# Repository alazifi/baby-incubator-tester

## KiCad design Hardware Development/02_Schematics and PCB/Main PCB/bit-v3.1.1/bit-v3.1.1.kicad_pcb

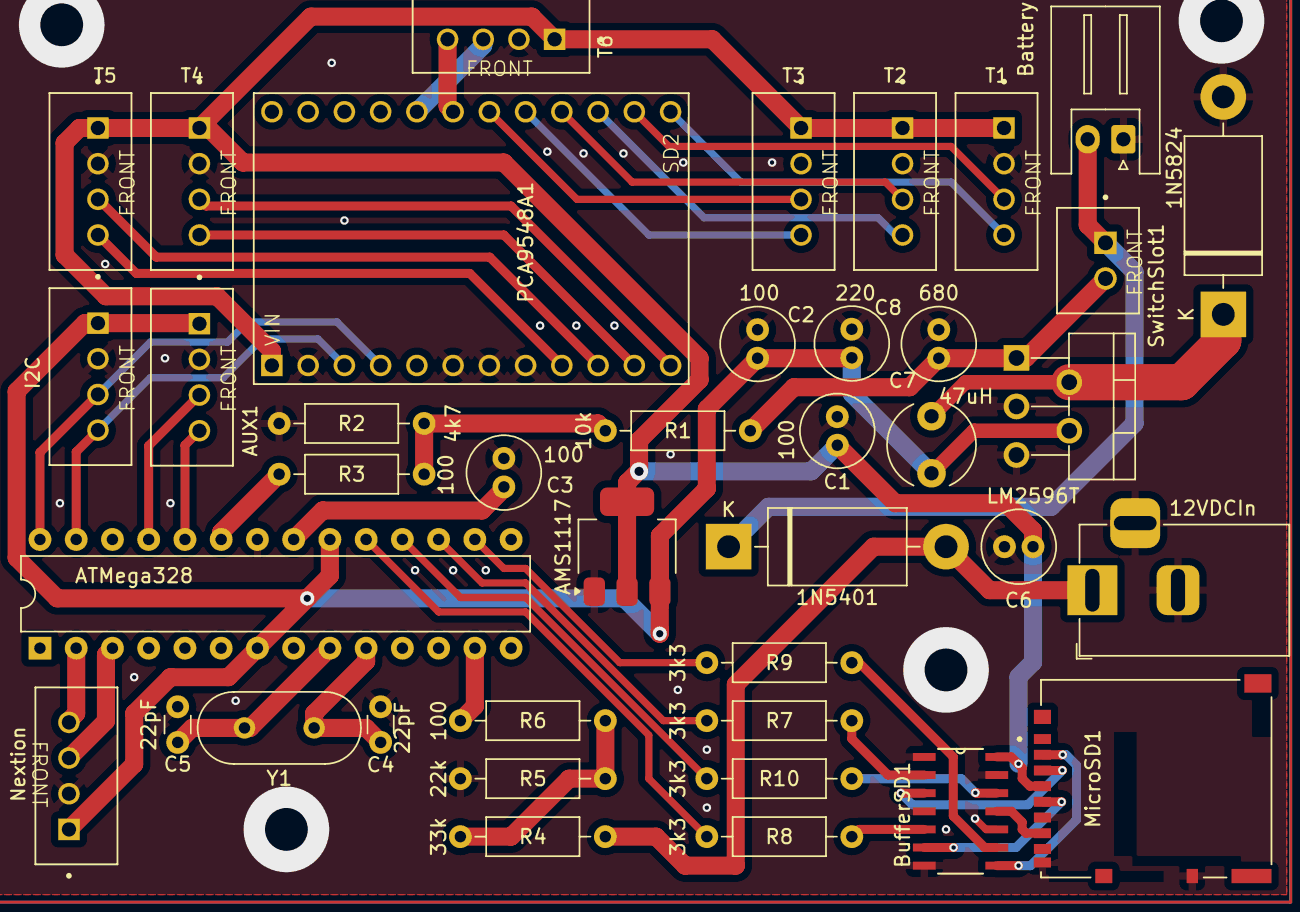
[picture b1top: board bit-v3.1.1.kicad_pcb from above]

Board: 2 copper layers, 40 parts (0 on the bottom side), 44 nets.

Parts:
1N5401: 1N5401; D_DO-201AD_P15.24mm_Horizontal
1N5824: 1N5824; D_DO-201AD_P15.24mm_Horizontal
12VDCIn: 12VDC In; BarrelJack_Horizontal
47uH: 47; L_Radial_D6.0mm_P4.00mm
AMS1117: AMS1117; SOT-223-3_TabPin2
ATMega328: ATmega328P-P; DIP-28_W7.62mm
AUX1: AUX; JST_B4B-XH-A_LF__SN_
Battery: Battery; JST_XH_S2B-XH-A_1x02_P2.50mm_Horizontal
BufferSD1: IC-SD; SOIC127P600X175-14N
C1, C2, C3, C6: 100; C_Radial_D5.0mm_H11.0mm_P2.00mm
C4, C5: 22pF; C_Disc_D3.0mm_W1.6mm_P2.50mm
C7: 680; C_Radial_D5.0mm_H11.0mm_P2.00mm
C8: 220; C_Radial_D5.0mm_H11.0mm_P2.00mm
I2C: I2C; JST_B4B-XH-A_LF__SN_
LM2596T: LM2596T-5; TO-220-5_P3.4x3.7mm_StaggerOdd_Lead3.8mm_Vertical
MicroSD1: MicroSD; HRS_DM3AT-SF-PEJM5
Nextion: Nextion; JST_B4B-XH-A_LF__SN_
PCA9548A1: PCA9548A_Board; PCA9548A
R1: 10k; R_Axial_DIN0207_L6.3mm_D2.5mm_P10.16mm_Horizontal
R2: 4k7; R_Axial_DIN0207_L6.3mm_D2.5mm_P10.16mm_Horizontal
R3, R6: 100; R_Axial_DIN0207_L6.3mm_D2.5mm_P10.16mm_Horizontal
R4: 33k; R_Axial_DIN0207_L6.3mm_D2.5mm_P10.16mm_Horizontal
R5: 22k; R_Axial_DIN0207_L6.3mm_D2.5mm_P10.16mm_Horizontal
R7, R8, R9, R10: 3k3; R_Axial_DIN0207_L6.3mm_D2.5mm_P10.16mm_Horizontal
SwitchSlot1: Switch; JST_B2B-XH-A
T1: T1; JST_B4B-XH-A_LF__SN_
T2: T2; JST_B4B-XH-A_LF__SN_
T3: T3; JST_B4B-XH-A_LF__SN_
T4: T4; JST_B4B-XH-A_LF__SN_
T5: T5; JST_B4B-XH-A_LF__SN_
T6: T6; JST_B4B-XH-A_LF__SN_
Y1: Crystal; Crystal_HC49-4H_Vertical

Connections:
3V3DC: AMS1117.2 (VO), BufferSD1.14 (VCC), C1.1, C6.1, MicroSD1.4 (VDD), PCA9548A1.1 (VIN), T1.1, T2.1, T3.1, T4.1, T5.1, T6.1
5VDC: 47uH.2, AMS1117.3 (VI), ATMega328.7 (VCC), ATMega328.20 (AVCC), AUX1.1, C2.1, C8.1, I2C.1, LM2596T.4 (FB), Nextion.1
AUX1: ATMega328.24 (PC1), AUX1.4
AUX2: ATMega328.25 (PC2), AUX1.3
Bat_Measure: ATMega328.23 (PC0), R3.1
CLK: ATMega328.19 (PB5), R8.1
CLK_L: BufferSD1.6 (O1), MicroSD1.5 (CLK)
CS: ATMega328.16 (PB2), R9.1
CS_L: BufferSD1.8 (O3), MicroSD1.2 (DAT3/CD)
Chg_Indicator: ATMega328.13 (PD7), R6.1
GND: 1N5824.2 (A), 12VDCIn.2, 12VDCIn.3, AMS1117.1 (GND), ATMega328.8 (GND), ATMega328.22 (GND), AUX1.2, Battery.1, BufferSD1.1 (~A0), BufferSD1.4 (~A1), BufferSD1.7 (GND), BufferSD1.10 (~A3), BufferSD1.13 (~A2), C1.2, C2.2, C3.2, C4.2, C5.2, C6.2, C7.2, C8.2, I2C.2, LM2596T.3 (GND), LM2596T.5 (~ON/OFF), MicroSD1.6 (VSS), MicroSD1.9 (SHIELD), Nextion.2, PCA9548A1.2 (GND), PCA9548A1.6 (A0), PCA9548A1.7 (A1), PCA9548A1.8 (A2), R2.2, R5.2, T1.2, T2.2, T3.2, T4.2, T5.2, T6.2
MISO: ATMega328.18 (PB4), R10.1
MISO_L: BufferSD1.11 (O2), MicroSD1.7 (DAT0)
MOSI: ATMega328.17 (PB3), R7.1
MOSI_L: BufferSD1.3 (O0), MicroSD1.3 (CMD)
unnamed: 1N5401.2 (A), 12VDCIn.1, R4.1
unnamed: 1N5401.1 (K), Battery.2, SwitchSlot1.1
unnamed: 1N5824.1 (K), 47uH.1, LM2596T.2 (OUT)
unnamed: ATMega328.21 (AREF), C3.1
unnamed: ATMega328.9 (XTAL1/PB6), C5.1, Y1.2
unnamed: ATMega328.10 (XTAL2/PB7), C4.1, Y1.1
unnamed: BufferSD1.2 (B0), R7.2
unnamed: BufferSD1.5 (B1), R8.2
unnamed: BufferSD1.12 (B2), R10.2
unnamed: BufferSD1.9 (B3), R9.2
unnamed: R1.2, R2.1, R3.2
unnamed: R4.2, R5.1, R6.2
RX: ATMega328.2 (PD0), Nextion.4
SCL: ATMega328.28 (PC5), I2C.3, PCA9548A1.4 (SCL)
SCL0: PCA9548A1.14 (SC2), T1.3
SCL1: PCA9548A1.16 (SC3), T2.3
SCL2: PCA9548A1.18 (SC4), T3.3
SCL3: PCA9548A1.12 (SC1), T4.3
SCL4: PCA9548A1.10 (SC0), T5.3
SCL5: PCA9548A1.20 (SC5), T6.3
SDA: ATMega328.27 (PC4), I2C.4, PCA9548A1.3 (SDA)
SDA0: PCA9548A1.13 (SD2), T1.4
SDA1: PCA9548A1.15 (SD3), T2.4
SDA2: PCA9548A1.17 (SD4), T3.4
SDA3: PCA9548A1.11 (SD1), T4.4
SDA4: PCA9548A1.9 (SD0), T5.4
SDA5: PCA9548A1.19 (SD5), T6.4
TX: ATMega328.3 (PD1), Nextion.3
VBatt: C7.1, LM2596T.1 (VIN), R1.1, SwitchSlot1.2

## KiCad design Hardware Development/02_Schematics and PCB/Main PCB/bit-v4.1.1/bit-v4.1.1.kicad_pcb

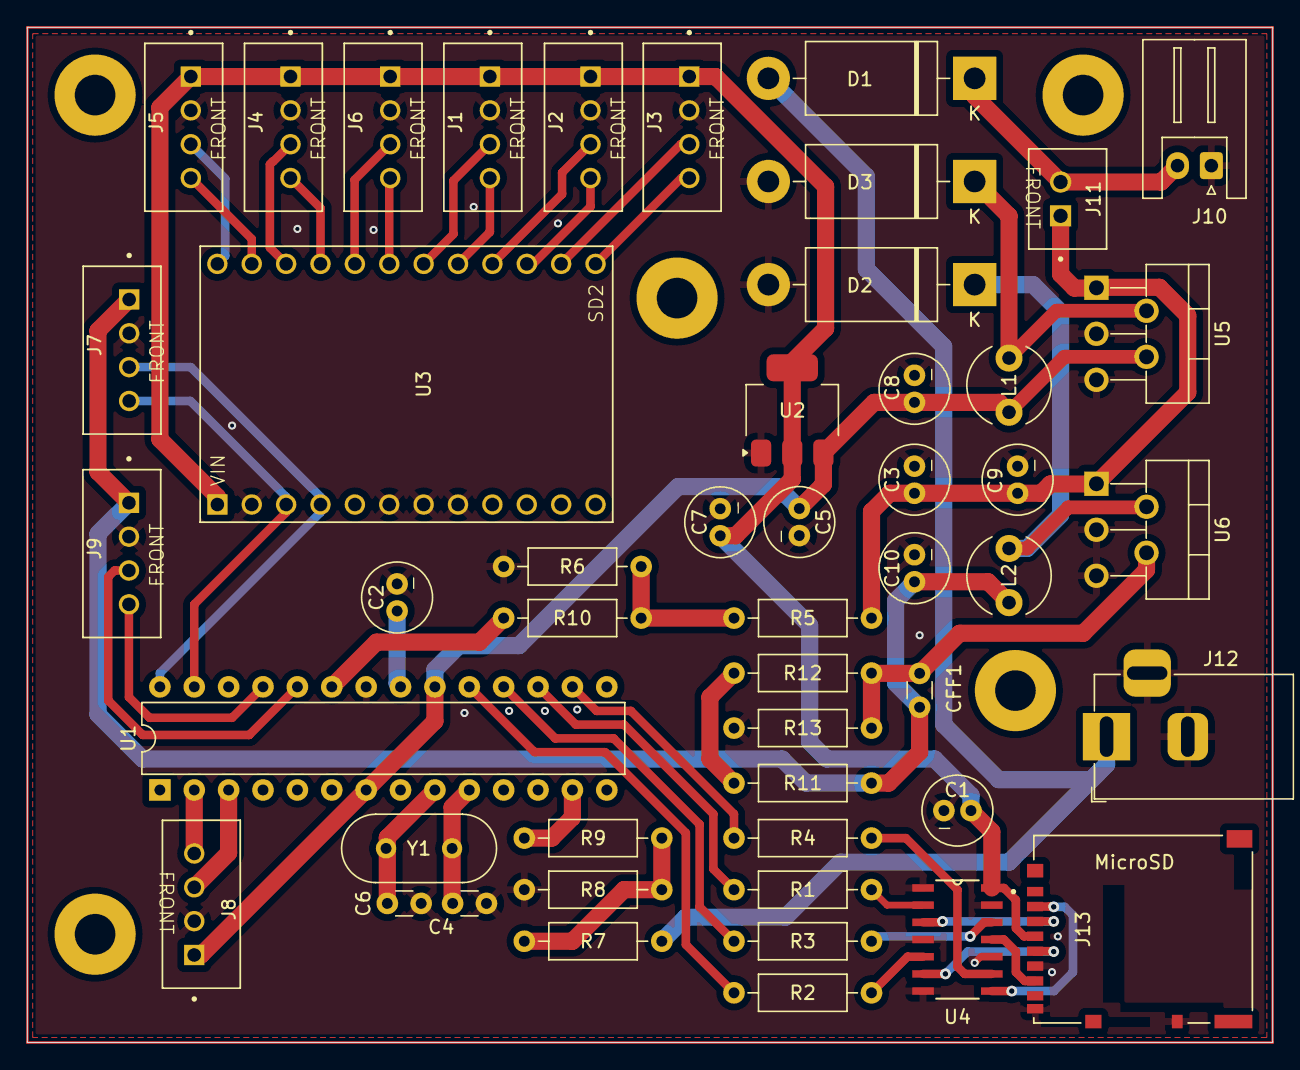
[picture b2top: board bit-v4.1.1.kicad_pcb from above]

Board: 2 copper layers, 92.0 x 75.0 mm, 49 parts (0 on the bottom side), 48 nets.

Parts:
C1, C2, C5, C7: 100; C_Radial_D5.0mm_H11.0mm_P2.00mm
C3, C9: 680; C_Radial_D5.0mm_H11.0mm_P2.00mm
C4, C6: 22pF; C_Disc_D3.0mm_W1.6mm_P2.50mm
C8: 220; C_Radial_D5.0mm_H11.0mm_P2.00mm
C10: 330; C_Radial_D5.0mm_H11.0mm_P2.00mm
CFF1: 1,5nF; C_Disc_D3.0mm_W1.6mm_P2.50mm
D1: 1N5401; D_DO-201AD_P15.24mm_Horizontal
D2, D3: 1N5825; D_DO-201AD_P15.24mm_Horizontal
J1: T1; JST_B4B-XH-A_LF__SN_
J2: T2; JST_B4B-XH-A_LF__SN_
J3: T3; JST_B4B-XH-A_LF__SN_
J4: T4; JST_B4B-XH-A_LF__SN_
J5: T5; JST_B4B-XH-A_LF__SN_
J6: T6; JST_B4B-XH-A_LF__SN_
J7: I2C; JST_B4B-XH-A_LF__SN_
J8: Nextion; JST_B4B-XH-A_LF__SN_
J9: AUX; JST_B4B-XH-A_LF__SN_
J10: Battery; JST_XH_S2B-XH-A_1x02_P2.50mm_Horizontal
J11: Switch; JST_B2B-XH-A
J12: 12VDC In; BarrelJack_Horizontal
J13: MicroSD; HRS_DM3AT-SF-PEJM5
L1, L2: 33; L_Radial_D6.0mm_P4.00mm
R1, R2, R3, R4: 3k3; R_Axial_DIN0207_L6.3mm_D2.5mm_P10.16mm_Horizontal
R5: 10k; R_Axial_DIN0207_L6.3mm_D2.5mm_P10.16mm_Horizontal
R6: 4k7; R_Axial_DIN0207_L6.3mm_D2.5mm_P10.16mm_Horizontal
R7: 33k; R_Axial_DIN0207_L6.3mm_D2.5mm_P10.16mm_Horizontal
R8: 22k; R_Axial_DIN0207_L6.3mm_D2.5mm_P10.16mm_Horizontal
R9, R10: 100; R_Axial_DIN0207_L6.3mm_D2.5mm_P10.16mm_Horizontal
R11, R12: 1k; R_Axial_DIN0207_L6.3mm_D2.5mm_P10.16mm_Horizontal
R13: 390; R_Axial_DIN0207_L6.3mm_D2.5mm_P10.16mm_Horizontal
U1: ATmega328P-P; DIP-28_W7.62mm
U2: AMS1117; SOT-223-3_TabPin2
U3: PCA9548A_Board; PCA9548A
U4: IC-SD; SOIC127P600X175-14N
U5: OUT-5V; TO-220-5_P3.4x3.7mm_StaggerOdd_Lead3.8mm_Vertical
U6: OUT-7,5V; TO-220-5_P3.4x3.7mm_StaggerOdd_Lead3.8mm_Vertical
Y1: Crystal; Crystal_HC49-4H_Vertical

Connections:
3V3DC: C1.1, C7.1, J1.1, J2.1, J3.1, J4.1, J5.1, J6.1, J13.4 (VDD), U2.2 (VO), U3.1 (VIN), U4.14 (VCC)
5VDC: C5.1, C8.1, J8.1, L1.2, U1.7 (VCC), U1.20 (AVCC), U2.3 (VI), U5.4 (FB)
7V5DC: C10.1, CFF1.1, J7.1, J9.1, L2.2, R11.1
AUX1: J9.3, U1.24 (PC1)
AUX2: J9.4, U1.25 (PC2)
Bat_Measure: R10.1, U1.23 (PC0)
CLK: R2.1, U1.19 (PB5)
CLK_L: J13.5 (CLK), U4.6 (O1)
CS: R4.1, U1.16 (PB2)
CS_L: J13.2 (DAT3/CD), U4.8 (O3)
Chg_Indicator: R9.1, U1.13 (PD7)
GND: C1.2, C2.2, C3.2, C4.2, C5.2, C6.2, C7.2, C8.2, C9.2, C10.2, D2.2 (A), D3.2 (A), J1.2, J2.2, J3.2, J4.2, J5.2, J6.2, J7.2, J8.2, J9.2, J10.1, J12.2, J12.3, J13.6 (VSS), J13.9 (SHIELD), R6.2, R8.2, R13.1, U1.8 (GND), U1.22 (GND), U2.1 (GND), U3.2 (GND), U3.6 (A0), U3.7 (A1), U3.8 (A2), U4.1 (~A0), U4.4 (~A1), U4.7 (GND), U4.10 (~A3), U4.13 (~A2), U5.3 (GND), U5.5 (~ON/OFF), U6.3 (GND), U6.5 (~ON-OFF)
MISO: R3.1, U1.18 (PB4)
MISO_L: J13.7 (DAT0), U4.11 (O2)
MOSI: R1.1, U1.17 (PB3)
MOSI_L: J13.3 (CMD), U4.3 (O0)
unnamed: D1.2 (A), J12.1, R7.1
unnamed: D1.1 (K), J10.2, J11.2
unnamed: D2.1 (K), L2.1, U6.2 (OUTPUT)
unnamed: D3.1 (K), L1.1, U5.2 (OUT)
unnamed: R7.2, R8.1, R9.2
unnamed: R5.2, R6.1, R10.2
unnamed: R11.2, R12.1
unnamed: C2.1, U1.21 (AREF)
unnamed: C6.1, U1.9 (XTAL1/PB6), Y1.2
unnamed: C4.1, U1.10 (XTAL2/PB7), Y1.1
unnamed: R1.2, U4.2 (B0)
unnamed: R2.2, U4.5 (B1)
unnamed: R3.2, U4.12 (B2)
unnamed: R4.2, U4.9 (B3)
unnamed: CFF1.2, R12.2, R13.2, U6.4 (FB)
RX: J8.4, U1.2 (PD0)
SCL: J7.3, U1.28 (PC5), U3.4 (SCL)
SCL0: J1.3, U3.18 (SC4)
SCL1: J2.3, U3.16 (SC3)
SCL2: J3.3, U3.14 (SC2)
SCL3: J4.3, U3.22 (SC6)
SCL4: J5.3, U3.24 (SC7)
SCL5: J6.3, U3.20 (SC5)
SDA: J7.4, U1.27 (PC4), U3.3 (SDA)
SDA0: J1.4, U3.17 (SD4)
SDA1: J2.4, U3.15 (SD3)
SDA2: J3.4, U3.13 (SD2)
SDA3: J4.4, U3.21 (SD6)
SDA4: J5.4, U3.23 (SD7)
SDA5: J6.4, U3.19 (SD5)
TX: J8.3, U1.3 (PD1)
VBatt: C3.1, C9.1, J11.1, R5.1, U5.1 (VIN), U6.1 (VIN)

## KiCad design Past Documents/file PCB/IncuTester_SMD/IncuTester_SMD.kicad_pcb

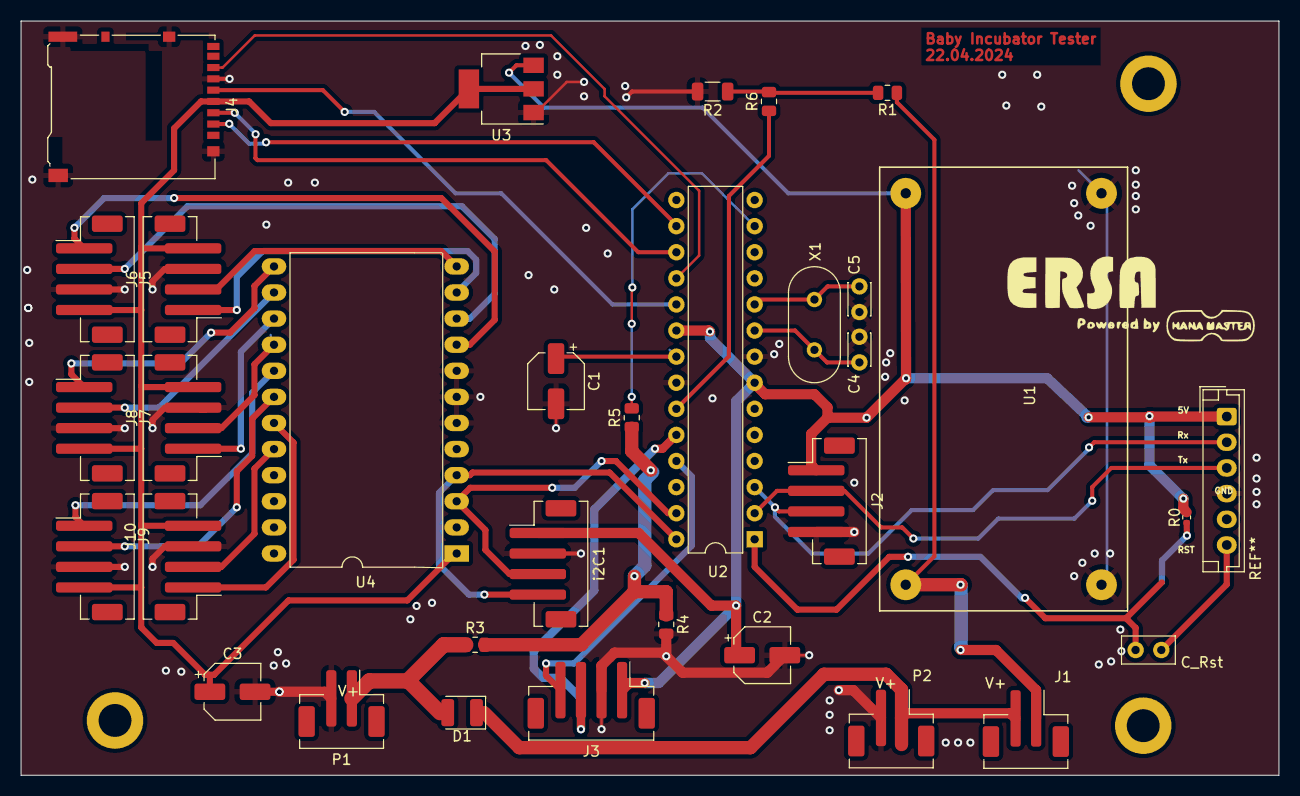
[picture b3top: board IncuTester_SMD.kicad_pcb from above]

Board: 2 copper layers, 122.4 x 73.4 mm, 32 parts (0 on the bottom side), 36 nets.

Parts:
C1, C2, C3: 100uF/10V; CP_Elec_5x5.4
C4, C5: 22p; C_Disc_D3.0mm_W2.0mm_P2.50mm
C_Rst: 0.1uF/10V; C_Disc_D5.0mm_W2.5mm_P2.50mm
D1: SMB(DO-214AA); D_1210_3225Metric
J1: SWITCH; JST_PH_B2B-PH-SM4-TB_1x02-1MP_P2.00mm_Vertical
J2: RS232; JST_PH_B4B-PH-SM4-TB_1x04-1MP_P2.00mm_Vertical
J3: AUX; JST_PH_B4B-PH-SM4-TB_1x04-1MP_P2.00mm_Vertical
J4: Micro_SD_Card; microSD_HC_Hirose_DM3AT-SF-PEJM5
J5: T3; JST_PH_B4B-PH-SM4-TB_1x04-1MP_P2.00mm_Vertical
J6: T4; JST_PH_B4B-PH-SM4-TB_1x04-1MP_P2.00mm_Vertical
J7: T5; JST_PH_B4B-PH-SM4-TB_1x04-1MP_P2.00mm_Vertical
J8: T6; JST_PH_B4B-PH-SM4-TB_1x04-1MP_P2.00mm_Vertical
J9: T7; JST_PH_B4B-PH-SM4-TB_1x04-1MP_P2.00mm_Vertical
J10: T8; JST_PH_B4B-PH-SM4-TB_1x04-1MP_P2.00mm_Vertical
P1: DC IN; JST_PH_B2B-PH-SM4-TB_1x02-1MP_P2.00mm_Vertical
P2: BATT; JST_PH_B2B-PH-SM4-TB_1x02-1MP_P2.00mm_Vertical
R0: 10k; R_0402_1005Metric
R1: 10K; R_0805_2012Metric
R2: 4K7; R_1206_3216Metric
R3: 33K, 0805W8F3302T5E; R_0805_2012Metric
R4: 22K; R_0805_2012Metric
R5: 100, 0805W8F3302T5E; R_0805_2012Metric
R6: 100; R_0805_2012Metric
U1: DC-DC
U2: ATmega328P-P; DIP-28_W7.62mm
U3: AMS1117-3.3; SOT-223-3_TabPin2
U4: TCA9548APWR; DIP-24_W15.24mm_LongPads
X1: Crystal; Crystal_HC18-U_Vertical
i2C1: J2; JST_PH_B4B-PH-SM4-TB_1x04-1MP_P2.00mm_Vertical

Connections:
3v3: C3.1, J4.4 (VDD), J5.4, J6.4, J7.4, J8.4, J9.4, J10.4, U3.2 (VO), U4.1 (VCC)
+5V: C2.1, J2.1, J3.1, R0.2, U1.3 (+5V), U2.7 (VCC), U2.20 (AVCC), U3.3 (VI), i2C1.1
/CS: J4.2 (DAT3/CD), U2.16 (PB2)
/MISO: J4.7 (DAT0), U2.18 (PB4)
/MOSI: J4.3 (CMD), U2.17 (PB3)
/SCLK: J4.5 (CLK), U2.19 (PB5)
GND: C1.2, C2.2, C3.2, C4.2, C5.2, J2.4, J3.2, J4.6 (VSS), J4.11, J5.3, J6.3, J7.3, J8.3, J9.3, J10.3, P1.2, P2.2, R2.2, R4.2, U1.2 (-IN), U1.4 (GND), U2.8 (GND), U2.22 (GND), U3.1 (GND), U4.2 (GND), U4.6 (A0), U4.7 (A1), U4.8 (A2), i2C1.2
unnamed: D1.2, P1.1, R3.1
unnamed: D1.1, J1.2, P2.1
unnamed: J1.1, R1.1, U1.1 (+IN)
unnamed: J2.3, U2.3 (PD1)
unnamed: J2.2, U2.2 (PD0)
unnamed: J3.3, U2.24 (PC1)
unnamed: J3.4, U2.25 (PC2)
unnamed: J5.1, U4.9 (SD0)
unnamed: J5.2, U4.10 (SC0)
unnamed: J6.1, U4.11 (SD1)
unnamed: J6.2, U4.12 (SC1)
unnamed: J7.1, U4.13 (SD2)
unnamed: J7.2, U4.14 (SC2)
unnamed: J8.1, U4.15 (SD3)
unnamed: J8.2, U4.16 (SC3)
unnamed: J9.1, U4.17 (SD4)
unnamed: J9.2, U4.18 (SC4)
unnamed: J10.1, U4.19 (SD5)
unnamed: J10.2, U4.20 (SC5)
unnamed: R1.2, R2.1, R6.2
unnamed: R3.2, R4.1, R5.1
unnamed: C1.1, U2.21 (AREF)
unnamed: R6.1, U2.23 (PC0)
unnamed: U2.27 (PC4), U4.3 (SDA), i2C1.3
unnamed: U2.28 (PC5), U4.4 (SCL), i2C1.4
unnamed: R5.2, U2.13 (PD7)
unnamed: C4.1, U2.9 (XTAL1/PB6), X1.1
unnamed: C5.1, U2.10 (XTAL2/PB7), X1.2
RST: C_Rst.1, R0.1, U2.1 (~RESET/PC6)
